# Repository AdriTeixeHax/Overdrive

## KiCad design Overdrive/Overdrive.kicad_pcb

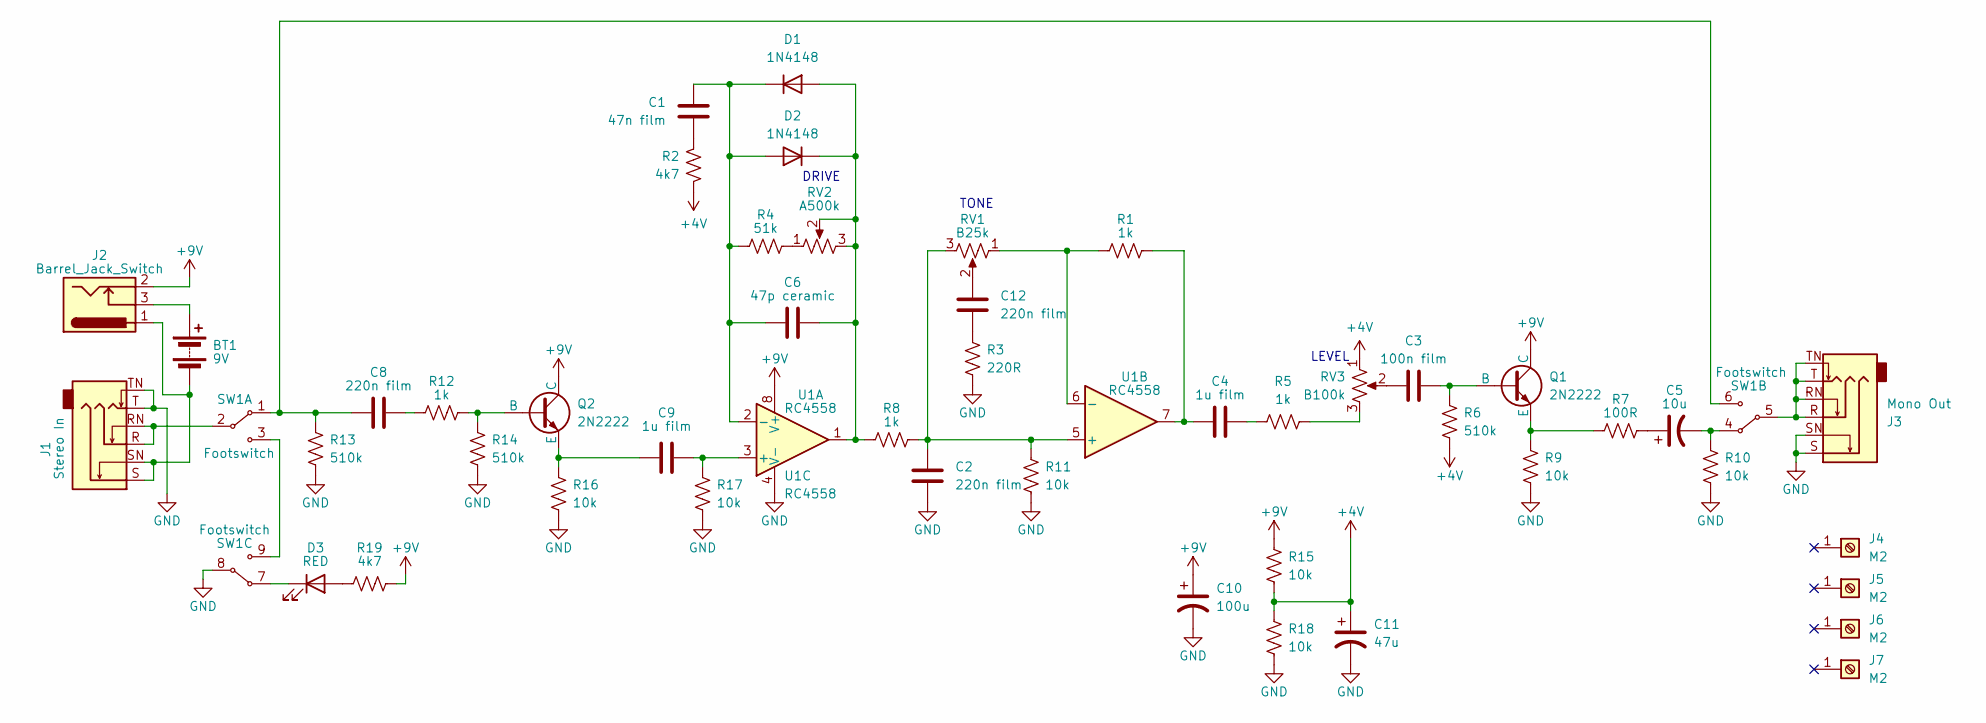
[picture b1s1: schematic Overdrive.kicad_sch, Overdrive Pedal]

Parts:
BT1: 9V; PinSocket_1x02_P2.54mm_Vertical
C1: 47n film; C_Rect_L7.0mm_W2.0mm_P5.00mm
C2, C8, C12: 220n film; C_Rect_L7.0mm_W2.0mm_P5.00mm
C3: 100n film; C_Rect_L7.0mm_W2.0mm_P5.00mm
C4, C9: 1u film; C_Rect_L7.0mm_W2.0mm_P5.00mm
C5: 10u; CP_Radial_D6.3mm_P2.50mm
C6: 47p ceramic; C_Disc_D5.0mm_W2.5mm_P5.00mm
C10: 100u; CP_Radial_D6.3mm_P2.50mm
C11: 47u; CP_Radial_D6.3mm_P2.50mm
D1, D2: 1N4148; D_DO-35_SOD27_P10.16mm_Horizontal
D3: RED; LED_D3.0mm
J1: Stereo In; Jack_6.35mm_Neutrik_NRJ6HM-1-AU_Horizontal
J2: Barrel_Jack_Switch; BarrelJack_Horizontal
J3: Mono Out; Jack_6.35mm_Neutrik_NRJ6HM-1-AU_Horizontal
J4, J5, J6, J7: M2; MountingHole_3.2mm_M3_DIN965_Pad
Q1, Q2: 2N2222; TO-92_Inline
R1, R5, R8, R12: 1k; R_Axial_DIN0309_L9.0mm_D3.2mm_P12.70mm_Horizontal
R2, R19: 4k7; R_Axial_DIN0309_L9.0mm_D3.2mm_P12.70mm_Horizontal
R3: 220R; R_Axial_DIN0309_L9.0mm_D3.2mm_P12.70mm_Horizontal
R4: 51k; R_Axial_DIN0309_L9.0mm_D3.2mm_P12.70mm_Horizontal
R6, R13, R14: 510k; R_Axial_DIN0309_L9.0mm_D3.2mm_P12.70mm_Horizontal
R7: 100R; R_Axial_DIN0309_L9.0mm_D3.2mm_P12.70mm_Horizontal
R9, R10, R11, R15, R16, R17, R18: 10k; R_Axial_DIN0309_L9.0mm_D3.2mm_P12.70mm_Horizontal
RV1: B25k; PinHeader_1x03_P2.54mm_Vertical
RV2: A500k; PinHeader_1x03_P2.54mm_Vertical
RV3: B100k; PinHeader_1x03_P2.54mm_Vertical
SW1: Footswitch
U1: RC4558; DIP-8_W7.62mm_Socket

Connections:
+4V: C11.1, R2.2, R6.2, R15.2, R18.1, RV3.1
+9V: C10.1, J2.2, Q1.1 (C), Q2.1 (C), R15.1, R19.2, U1.8 (V+)
GND: C2.2, C10.2, C11.2, J1.T, J1.TN, J3.S, J3.SN, R3.2, R9.2, R10.2, R11.2, R13.2, R14.2, R16.2, R17.2, R18.2, SW1.8, U1.4 (V-)
unnamed: BT1.1 (+), J2.3
unnamed: BT1.2 (-), J1.S, J1.SN, J2.1
unnamed: C1.2, R2.1
unnamed: C3.1, RV3.2
unnamed: C4.1, R1.2, U1.7
unnamed: C4.2, R5.1
unnamed: C5.1, R7.2
unnamed: C5.2, R10.1, SW1.4
unnamed: C8.1, R13.1, SW1.1, SW1.6
unnamed: C8.2, R12.1
unnamed: C12.1, RV1.2
unnamed: C12.2, R3.1
unnamed: C6.2, D1.2 (A), D2.1 (K), R8.1, RV2.2, RV2.3, U1.1
unnamed: C1.1, C6.1, D1.1 (K), D2.2 (A), R4.1, U1.2 (-)
unnamed: D3.2 (A), R19.1
unnamed: D3.1 (K), SW1.7
unnamed: J1.R, J1.RN, SW1.2
unnamed: J3.R, J3.RN, J3.T, J3.TN, SW1.5
unnamed: C3.2, Q1.2 (B), R6.1
unnamed: Q1.3 (E), R7.1, R9.1
unnamed: Q2.2 (B), R12.2, R14.1
unnamed: C9.1, Q2.3 (E), R16.1
unnamed: R4.2, RV2.1
unnamed: R5.2, RV3.3
unnamed: SW1.3, SW1.9
unnamed: C9.2, R17.1, U1.3 (+)
unnamed: C2.1, R8.2, R11.1, RV1.3, U1.5 (+)
unnamed: R1.1, RV1.1, U1.6 (-)

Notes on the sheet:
TONE
DRIVE
LEVEL

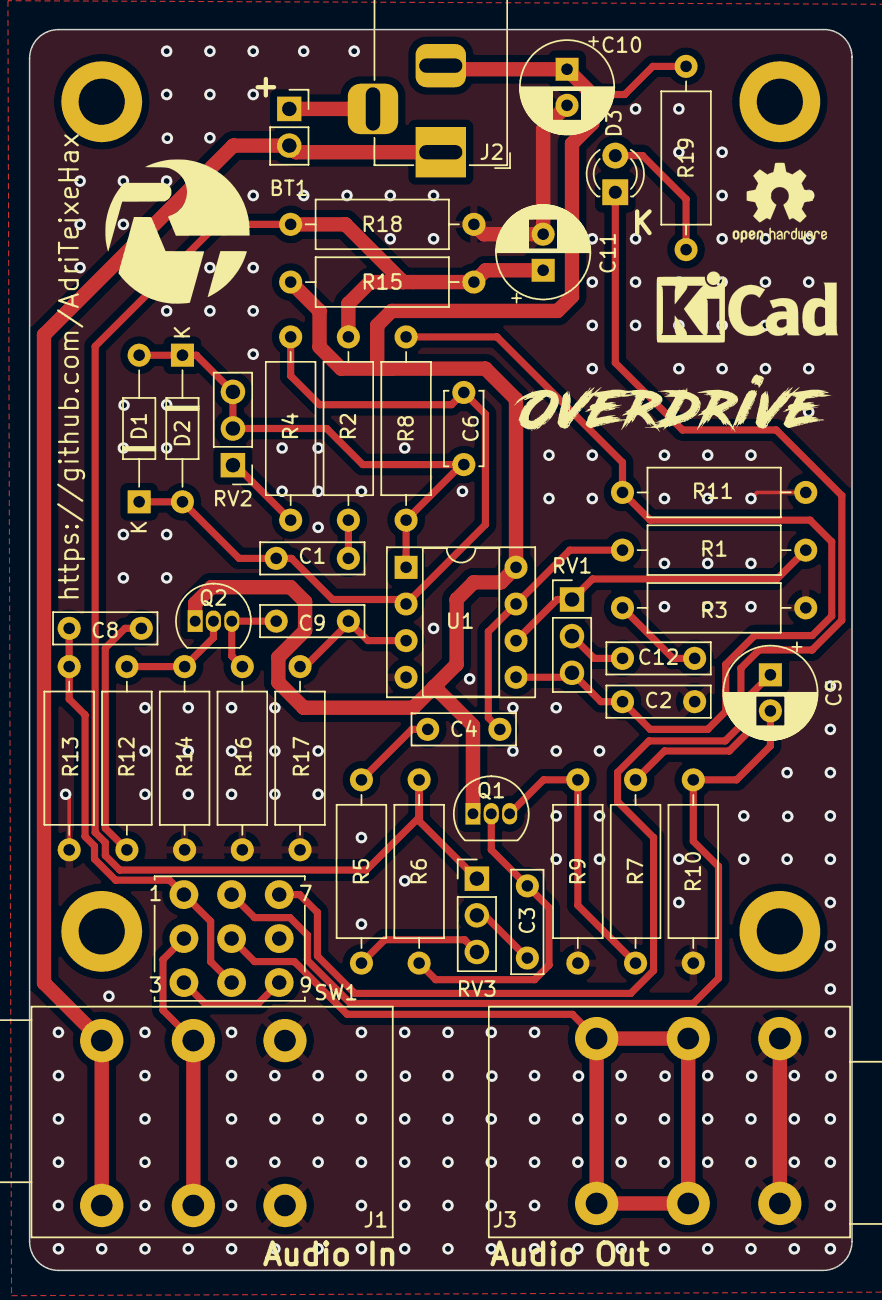
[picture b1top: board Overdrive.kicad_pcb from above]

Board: 2 copper layers, 57.0 x 86.0 mm, 48 parts (0 on the bottom side), 31 nets.

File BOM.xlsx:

|  |  |  |  |  |  | 7.8549999999999995
 | Ref | Qnty | Value | Component name | Footprint | €/ud | Total | Link | Description
 | BT1 | 1 | 9V | Battery | Connector_PinSocket_2.54mm:PinSocket_1x02_P2.54mm_Vertical | 9.0300000000000005E-2 | 9.0300000000000005E-2 | https://www.lcsc.com/product-detail/span-style-background-co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 | Multiple-cell battery
 | C1 | 1 | 47n film | C | Capacitor_THT:C_Rect_L7.0mm_W2.0mm_P5.00mm | 2.9700000000000001E-2 | 2.9700000000000001E-2 | https://www.lcsc.com/product-detail/Film-Capacitors_KYET-PE4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 | Unpolarized capacitor
 | C2, C8, C12 | 3 | 220n film | C | Capacitor_THT:C_Rect_L7.0mm_W2.0mm_P5.00mm | 5.0799999999999998E-2 | 0.15239999999999998 | https://www.lcsc.com/product-detail/Film-Capacitors_KYET-PE2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 | Unpolarized capacitor
 | C3 | 1 | 100n film | C | Capacitor_THT:C_Rect_L7.0mm_W2.0mm_P5.00mm | 3.61E-2 | 3.61E-2 | https://www.lcsc.com/product-detail/Film-Capacitors_KNSCHA-M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 | Unpolarized capacitor
 | C4, C9 | 2 | 1u film | C | Capacitor_THT:C_Rect_L7.0mm_W2.0mm_P5.00mm | 0.14080000000000001 | 0.28160000000000002 | https://www.lcsc.com/product-detail/Film-Capacitors_KNSCHA-M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 | Unpolarized capacitor
 | C5 | 1 | 10u | C_Polarized_US | Capacitor_THT:CP_Radial_D6.3mm_P2.50mm | 5.8599999999999999E-2 | 5.8599999999999999E-2 | https://www.lcsc.com/product-detail/Aluminum-Electrolytic-Ca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 | Polarized capacitor, US symbol
 | C6 | 1 | 47p ceramic | C | Capacitor_THT:C_Disc_D5.0mm_W2.5mm_P5.00mm | 1.24E-2 | 1.24E-2 | https://www.lcsc.com/product-detail/Ceramic-Disc-Capacitors_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 | Unpolarized capacitor
 | C10 | 1 | 100u | C_Polarized_US | Capacitor_THT:CP_Radial_D6.3mm_P2.50mm | 2.35E-2 | 2.35E-2 | https://www.lcsc.com/product-detail/Aluminum-Electrolytic-Ca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 | Polarized capacitor, US symbol
 | C11 | 1 | 47u | C_Polarized_US | Capacitor_THT:CP_Radial_D6.3mm_P2.50mm | 1.7899999999999999E-2 | 1.7899999999999999E-2 | https://www.lcsc.com/product-detail/Aluminum-Electrolytic-Ca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 | Polarized capacitor, US symbol
 | D1, D2 | 2 | 1N4148 | D | Diode_THT:D_DO-35_SOD27_P10.16mm_Horizontal | 7.3000000000000001E-3 | 1.46E-2 | https://www.lcsc.com/product-detail/Switching-Diode_LGE-1N41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 | Diode
 | D3 | 1 | RED | LED | LED_THT:LED_D3.0mm | 1.6E-2 | 1.6E-2 | https://www.lcsc.com/product-detail/Light-Emitting-Diodes-LE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 | Light emitting diode
 | J1, J3 | 2 | Stereo In, Mono Out | AudioJack3_Switch | Connector_Audio:Jack_6.35mm_Neutrik_NRJ6HM-1-AU_Horizontal | 0.432 | 0.86399999999999999 | https://www.lcsc.com/product-detail/Audio-Connectors_HOOYA-P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 | Audio Jack, 3 Poles (Stereo / TRS), Switched Poles (Normalling)
 | J2 | 1 | Barrel_Jack_Switch | Barrel_Jack_Switch | Connector_BarrelJack:BarrelJack_Horizontal | 4.6100000000000002E-2 | 4.6100000000000002E-2 | https://www.lcsc.com/product-detail/AC-DC-Power-Connectors_B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 | DC Barrel Jack with an internal switch
 | Q1, Q2 | 2 | 2N2222 | NPN | Package_TO_SOT_THT:TO-92_Inline | 1.44E-2 | 2.8799999999999999E-2 | https://www.lcsc.com/product-detail/Bipolar-Transistors-BJT_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 | Bipolar transistor symbol for simulation only, substrate tied to the emitter
 | R1, R5, R8, R12 | 4 | 1k | R_US | Resistor_THT:R_Axial_DIN0309_L9.0mm_D3.2mm_P12.70mm_Horizontal | 5.7000000000000002E-3 | 2.2800000000000001E-2 | https://www.lcsc.com/product-detail/Through-Hole-Resistors_H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 | Resistor, US symbol
 | R2, R19 | 2 | 4k7 | R_US | Resistor_THT:R_Axial_DIN0309_L9.0mm_D3.2mm_P12.70mm_Horizontal | 4.7000000000000002E-3 | 9.4000000000000004E-3 | https://www.lcsc.com/product-detail/Through-Hole-Resistors_C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 | Resistor, US symbol
 | R3 | 1 | 220R | R_US | Resistor_THT:R_Axial_DIN0309_L9.0mm_D3.2mm_P12.70mm_Horizontal | 4.7000000000000002E-3 | 4.7000000000000002E-3 | https://www.lcsc.com/product-detail/Through-Hole-Resistors_C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 | Resistor, US symbol
 | R4 | 1 | 51k | R_US | Resistor_THT:R_Axial_DIN0309_L9.0mm_D3.2mm_P12.70mm_Horizontal | 3.5999999999999999E-3 | 3.5999999999999999E-3 | https://www.lcsc.com/product-detail/Through-Hole-Resistors_V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 | Resistor, US symbol
 | R6, R13, R14 | 3 | 510k | R_US | Resistor_THT:R_Axial_DIN0309_L9.0mm_D3.2mm_P12.70mm_Horizontal | 1.3299999999999999E-2 | 3.9899999999999998E-2 | https://www.lcsc.com/product-detail/Through-Hole-Resistors_Y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 | Resistor, US symbol
 | R7 | 1 | 100R | R_US | Resistor_THT:R_Axial_DIN0309_L9.0mm_D3.2mm_P12.70mm_Horizontal | 0.1792 | 0.1792 | https://www.lcsc.com/product-detail/Through-Hole-Resistors_V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 | Resistor, US symbol
 | R9, R10, R11, R15, R16, R17, R18 | 7 | 10k | R_US | Resistor_THT:R_Axial_DIN0309_L9.0mm_D3.2mm_P12.70mm_Horizontal | 8.0999999999999996E-3 | 5.67E-2 | https://www.lcsc.com/product-detail/Through-Hole-Resistors_T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 | Resistor, US symbol
 | RV1 | 1 | B25k | R_Potentiometer_US | Connector_PinHeader_2.54mm:PinHeader_1x03_P2.54mm_Vertical | 0.28000000000000003 | 0.28000000000000003 | https://es.aliexpress.com/item/1005006314712451.html?spm=a2g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 | Potentiometer, US symbol
 | RV2 | 1 | A500k | R_Potentiometer_US | Connector_PinHeader_2.54mm:PinHeader_1x03_P2.54mm_Vertical | 0.26 | 0.26 | https://es.aliexpress.com/item/1005006314712451.html?spm=a2g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 | Potentiometer, US symbol
 | RV3 | 1 | B100k | R_Potentiometer_US | Connector_PinHeader_2.54mm:PinHeader_1x03_P2.54mm_Vertical | 0.28999999999999998 | 0.28999999999999998 | https://es.aliexpress.com/item/1005006314712451.html?spm=a2g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 | Potentiometer, US symbol
 | SW1 | 1 | Footswitch | 3PDT-ind | Switches:Footswitch | 1.01 | 1.01 | https://es.aliexpress.com/item/4000285680608.html?spm=a2g0o.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
 | U1 | 1 | RC4558 | RC4558 | Package_DIP:DIP-8_W7.62mm_Socket | 7.3200000000000001E-2 | 7.3200000000000001E-2 | https://www.lcsc.com/product-detail/Operational-Amplifier_YW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 | Dual General Purpose, Operational Amplifier, DIP-8/SOIC-8/SSOP-8
 | SCK1 | 1 | DIP-8 Socket |  | Package_DIP:DIP-8_W7.62mm_Socket | 2.35E-2 | 2.35E-2 | https://www.lcsc.com/product-detail/IC-Sockets_CONNFLY-Elec-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 | IC Socket DIP-8
 | PCB | 1 | PCB |  |  | 3.93 | 3.93 | JLCPCB
 |  |  |  |  |  |  | 0
 |  |  |  |  |  |  | 0
 | J4, J5, J6, J7 | 4 | M3 | Screw_Terminal_01x01 | MountingHole:MountingHole_3.2mm_M3_DIN965_Pad |  | 0 |  | Generic screw terminal, single row, 01x01, script generated (kicad-library-util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
 |  |  |  |  |  |  | 0
 |  |  |  |  |  |  | 0
 |  |  |  |  |  |  | 0
 |  |  |  |  |  |  | 0
 |  |  |  |  |  |  | 0
 |  |  |  |  |  |  | 0
 |  |  |  |  |  |  | 0
 |  |  |  |  |  |  | 0
 |  |  |  |  |  |  | 0
 |  |  |  |  |  |  | 0
 |  |  |  |  |  |  | 0
 |  |  |  |  |  |  | 0
 |  |  |  |  |  |  | 0
 |  |  |  |  |  |  | 0
 |  |  |  |  |  |  | 0
 |  |  |  |  |  |  | 0
 |  |  |  |  |  |  | 0
 |  |  |  |  |  |  | 0

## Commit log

2024-01-20 Added Schematics and a first version PCB
2024-01-21 Fixed schematic errors
2024-01-21 Fixed PCB errors and added logos
2024-01-21 Replaced wrl models with step models
2024-01-21 Redesigned board to fit 125B case
2024-01-22 added bom, gerber files and fixed last errors in pcb
2024-02-14 minor changes
2024-06-05 error correction in switches
